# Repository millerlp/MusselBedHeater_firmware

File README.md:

# MusselBedHeater_firmware
Luke Miller, 2020

A permanent archive of this repository is stored in a Zenodo archive: https://doi.org/10.5281/zenodo.7246441 

 Firmware and hardware for Mussel Bed Heater project that Claire Windecker carried out 
 for her Masters thesis at Cal Poly Humboldt. The project consists of a circuit board 
 design that uses Arduino software to control an ATmega328P microcontroller to carry out 
 temperature monitoring and control heated artificial mussel beds. 

## Hardware design files 

Hardware_files/ contains parts lists, bill of materials, and Autocad Eagle design files. MusselBedHeater_RevG is the
most recent version, and contains all of the modifications made to the Revision F boards that were used 
in the field experiment. The heater sub-assembly board is in Heater_subassembly_revA.

## Arduino software files 

library_copies/ contains copies of the necessary Arduino libraries used to run the MusselBedHeater_firmware

Arduino programs used to run the hardware in the field are contained in:
* MusselBedHeater_6Crise/
* MusselBedHeater_field/

Utility Arduino programs used to set up the boards initially are in:
* serial_number_generator/
* settime_Serial/

### Reference mussels

Part of the design included the need to have a reference temperature, which the heated mussels would then 
be heated above by 2C or 6C. Reference mussels used a MAX31820 OneWire temperature sensor, which was 
embedded in artificial epoxy mussels as well. One control board can monitor 4 reference temperature sensors. 
The software averages the temperatures from the available reference mussels and uses that value to establish
the 'ambient' mussel temperature. Heated mussels were then heated to a target temperature increase, 2 or 6 degrees
Celsius above ambient. 

A TO-92 package MAX31820 is shown wired into the cable that will lead back to the battery box and controller board.

## Heating assembly 

The heated artificial mussels were built using 38 Gauge Nichrome 80 wire (14 ohm per meter) in a 
length of 300 mm (~12 inches) wrapped around the Heater_subassembly_revA circuit board. This arrangement
should consume a maximum of about 3 Watts at 13V supply, but the circuit board is designed to pulse width
modulate the supply voltage to the heater and provide a basic PID control algorithm to achieve a desired 
target temperature above ambient. 

The cable supplying power to the heater coil also connected to a 6800 ohm 3% NTC thermistor, which was
used to measure the temperature of the artificial mussel. The thermistor was wired in a half-bridge
configured with 4700 ohm precision resistors found on the main MusselBedHeater_RevG circuit board.

The thermistor and heater coil board were eventually cast into the middle of an epoxy artificial mussel. 

One control board can control up to 16 heated mussels, including measuring their thermistor temperatures.

## Acknowledgements 
Funding from the National Science Foundation grants OCE-1904184 and OCE-1904185 helped support Luke Miller 
during the development of this hardware and software.

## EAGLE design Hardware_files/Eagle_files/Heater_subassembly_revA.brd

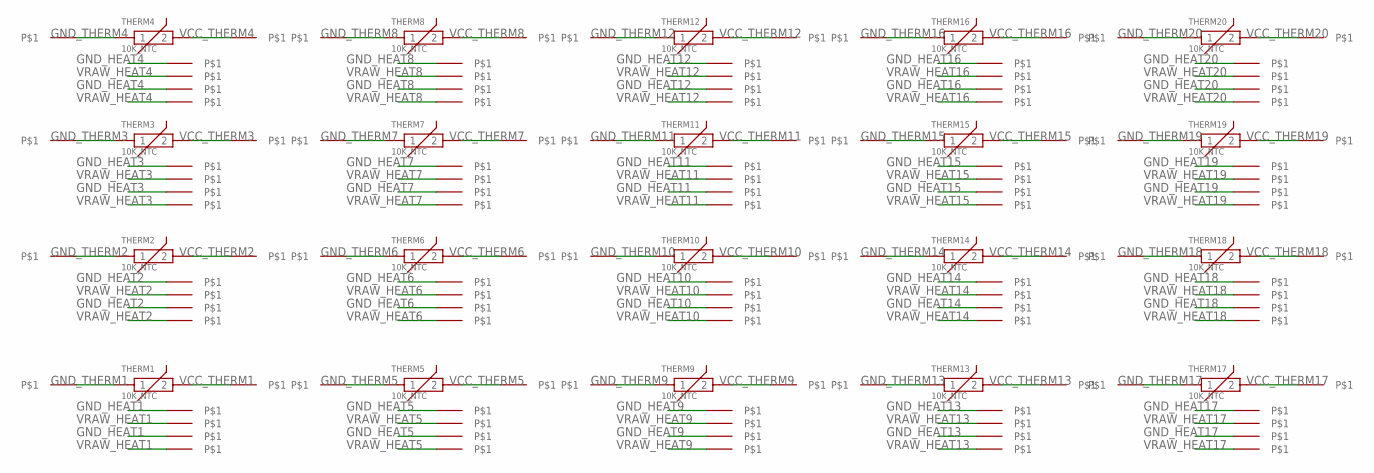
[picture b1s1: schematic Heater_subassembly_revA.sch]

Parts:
GND_HEAT1, GND_HEAT2, GND_HEAT3, GND_HEAT4, GND_HEAT5, GND_HEAT6, GND_HEAT7, GND_HEAT8, GND_HEAT9, GND_HEAT10, GND_HEAT11, GND_HEAT12, GND_HEAT13, GND_HEAT14, GND_HEAT15, GND_HEAT16, GND_HEAT17, GND_HEAT18, GND_HEAT19, GND_HEAT20: PINHD-1X1SMALL; 1X01_SMALL
GND_NICHROME1, GND_NICHROME2, GND_NICHROME3, GND_NICHROME4, GND_NICHROME5, GND_NICHROME6, GND_NICHROME7, GND_NICHROME8, GND_NICHROME9, GND_NICHROME10, GND_NICHROME11, GND_NICHROME12, GND_NICHROME13, GND_NICHROME14, GND_NICHROME15, GND_NICHROME16, GND_NICHROME17, GND_NICHROME18, GND_NICHROME19, GND_NICHROME20: PINHD-1X10.7MM_DRILL; 1X01_SMALL_0.7
GND_THERM1, GND_THERM2, GND_THERM3, GND_THERM4, GND_THERM5, GND_THERM6, GND_THERM7, GND_THERM8, GND_THERM9, GND_THERM10, GND_THERM11, GND_THERM12, GND_THERM13, GND_THERM14, GND_THERM16, GND_THERM17, GND_THERM18, GND_THERM19, GND_THERM20: PINHD-1X1SMALL; 1X01_SMALL
THERM1, THERM2, THERM3, THERM4, THERM5, THERM6, THERM7, THERM8, THERM9, THERM10, THERM11, THERM12, THERM13, THERM14, THERM15, THERM16, THERM17, THERM18, THERM19, THERM20: 10K_NTC; R0603_THERMISTOR
U$30: PINHD-1X1SMALL; 1X01_SMALL
VCC_THERM1, VCC_THERM2, VCC_THERM3, VCC_THERM4, VCC_THERM5, VCC_THERM6, VCC_THERM7, VCC_THERM8, VCC_THERM9, VCC_THERM10, VCC_THERM11, VCC_THERM12, VCC_THERM13, VCC_THERM14, VCC_THERM15, VCC_THERM16, VCC_THERM17, VCC_THERM18, VCC_THERM19, VCC_THERM20: PINHD-1X1SMALL; 1X01_SMALL
VRAW_HEAT1, VRAW_HEAT2, VRAW_HEAT3, VRAW_HEAT4, VRAW_HEAT5, VRAW_HEAT6, VRAW_HEAT7, VRAW_HEAT8, VRAW_HEAT9, VRAW_HEAT10, VRAW_HEAT11, VRAW_HEAT12, VRAW_HEAT13, VRAW_HEAT14, VRAW_HEAT15, VRAW_HEAT16, VRAW_HEAT17, VRAW_HEAT18, VRAW_HEAT19, VRAW_HEAT20: PINHD-1X1SMALL; 1X01_SMALL
VRAW_NICHROME1, VRAW_NICHROME2, VRAW_NICHROME3, VRAW_NICHROME4, VRAW_NICHROME5, VRAW_NICHROME6, VRAW_NICHROME7, VRAW_NICHROME8, VRAW_NICHROME9, VRAW_NICHROME10, VRAW_NICHROME11, VRAW_NICHROME12, VRAW_NICHROME13, VRAW_NICHROME14, VRAW_NICHROME15, VRAW_NICHROME16, VRAW_NICHROME17, VRAW_NICHROME18, VRAW_NICHROME19, VRAW_NICHROME20: PINHD-1X10.7MM_DRILL; 1X01_SMALL_0.7

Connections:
GND_HEAT1: GND_HEAT1.1, GND_NICHROME1.P$1
GND_HEAT2: GND_HEAT2.1, GND_NICHROME2.P$1
GND_HEAT3: GND_HEAT3.1, GND_NICHROME3.P$1
GND_HEAT4: GND_HEAT4.1, GND_NICHROME4.P$1
GND_HEAT5: GND_HEAT5.1, GND_NICHROME5.P$1
GND_HEAT6: GND_HEAT6.1, GND_NICHROME6.P$1
GND_HEAT7: GND_HEAT7.1, GND_NICHROME7.P$1
GND_HEAT8: GND_HEAT8.1, GND_NICHROME8.P$1
GND_HEAT9: GND_HEAT9.1, GND_NICHROME9.P$1
GND_HEAT10: GND_HEAT10.1, GND_NICHROME10.P$1
GND_HEAT11: GND_HEAT11.1, GND_NICHROME11.P$1
GND_HEAT12: GND_HEAT12.1, GND_NICHROME12.P$1
GND_HEAT13: GND_HEAT13.1, GND_NICHROME13.P$1
GND_HEAT14: GND_HEAT14.1, GND_NICHROME14.P$1
GND_HEAT15: GND_HEAT15.1, GND_NICHROME15.P$1
GND_HEAT16: GND_HEAT16.1, GND_NICHROME16.P$1
GND_HEAT17: GND_HEAT17.1, GND_NICHROME17.P$1
GND_HEAT18: GND_HEAT18.1, GND_NICHROME18.P$1
GND_HEAT19: GND_HEAT19.1, GND_NICHROME19.P$1
GND_HEAT20: GND_HEAT20.1, GND_NICHROME20.P$1
GND_THERM1: GND_THERM1.1, THERM1.1
GND_THERM2: GND_THERM2.1, THERM2.1
GND_THERM3: GND_THERM3.1, THERM3.1
GND_THERM4: GND_THERM4.1, THERM4.1
GND_THERM5: GND_THERM5.1, THERM5.1
GND_THERM6: GND_THERM6.1, THERM6.1
GND_THERM7: GND_THERM7.1, THERM7.1
GND_THERM8: GND_THERM8.1, THERM8.1
GND_THERM9: GND_THERM9.1, THERM9.1
GND_THERM10: GND_THERM10.1, THERM10.1
GND_THERM11: GND_THERM11.1, THERM11.1
GND_THERM12: GND_THERM12.1, THERM12.1
GND_THERM13: GND_THERM13.1, THERM13.1
GND_THERM14: GND_THERM14.1, THERM14.1
GND_THERM15: THERM15.1, U$30.1
GND_THERM16: GND_THERM16.1, THERM16.1
GND_THERM17: GND_THERM17.1, THERM17.1
GND_THERM18: GND_THERM18.1, THERM18.1
GND_THERM19: GND_THERM19.1, THERM19.1
GND_THERM20: GND_THERM20.1, THERM20.1
VCC_THERM1: THERM1.2, VCC_THERM1.1
VCC_THERM2: THERM2.2, VCC_THERM2.1
VCC_THERM3: THERM3.2, VCC_THERM3.1
VCC_THERM4: THERM4.2, VCC_THERM4.1
VCC_THERM5: THERM5.2, VCC_THERM5.1
VCC_THERM6: THERM6.2, VCC_THERM6.1
VCC_THERM7: THERM7.2, VCC_THERM7.1
VCC_THERM8: THERM8.2, VCC_THERM8.1
VCC_THERM9: THERM9.2, VCC_THERM9.1
VCC_THERM10: THERM10.2, VCC_THERM10.1
VCC_THERM11: THERM11.2, VCC_THERM11.1
VCC_THERM12: THERM12.2, VCC_THERM12.1
VCC_THERM13: THERM13.2, VCC_THERM13.1
VCC_THERM14: THERM14.2, VCC_THERM14.1
VCC_THERM15: THERM15.2, VCC_THERM15.1
VCC_THERM16: THERM16.2, VCC_THERM16.1
VCC_THERM17: THERM17.2, VCC_THERM17.1
VCC_THERM18: THERM18.2, VCC_THERM18.1
VCC_THERM19: THERM19.2, VCC_THERM19.1
VCC_THERM20: THERM20.2, VCC_THERM20.1
VRAW_HEAT1: VRAW_HEAT1.1, VRAW_NICHROME1.P$1
VRAW_HEAT2: VRAW_HEAT2.1, VRAW_NICHROME2.P$1
VRAW_HEAT3: VRAW_HEAT3.1, VRAW_NICHROME3.P$1
VRAW_HEAT4: VRAW_HEAT4.1, VRAW_NICHROME4.P$1
VRAW_HEAT5: VRAW_HEAT5.1, VRAW_NICHROME5.P$1
VRAW_HEAT6: VRAW_HEAT6.1, VRAW_NICHROME6.P$1
VRAW_HEAT7: VRAW_HEAT7.1, VRAW_NICHROME7.P$1
VRAW_HEAT8: VRAW_HEAT8.1, VRAW_NICHROME8.P$1
VRAW_HEAT9: VRAW_HEAT9.1, VRAW_NICHROME9.P$1
VRAW_HEAT10: VRAW_HEAT10.1, VRAW_NICHROME10.P$1
VRAW_HEAT11: VRAW_HEAT11.1, VRAW_NICHROME11.P$1
VRAW_HEAT12: VRAW_HEAT12.1, VRAW_NICHROME12.P$1
VRAW_HEAT13: VRAW_HEAT13.1, VRAW_NICHROME13.P$1
VRAW_HEAT14: VRAW_HEAT14.1, VRAW_NICHROME14.P$1
VRAW_HEAT15: VRAW_HEAT15.1, VRAW_NICHROME15.P$1
VRAW_HEAT16: VRAW_HEAT16.1, VRAW_NICHROME16.P$1
VRAW_HEAT17: VRAW_HEAT17.1, VRAW_NICHROME17.P$1
VRAW_HEAT18: VRAW_HEAT18.1, VRAW_NICHROME18.P$1
VRAW_HEAT19: VRAW_HEAT19.1, VRAW_NICHROME19.P$1
VRAW_HEAT20: VRAW_HEAT20.1, VRAW_NICHROME20.P$1

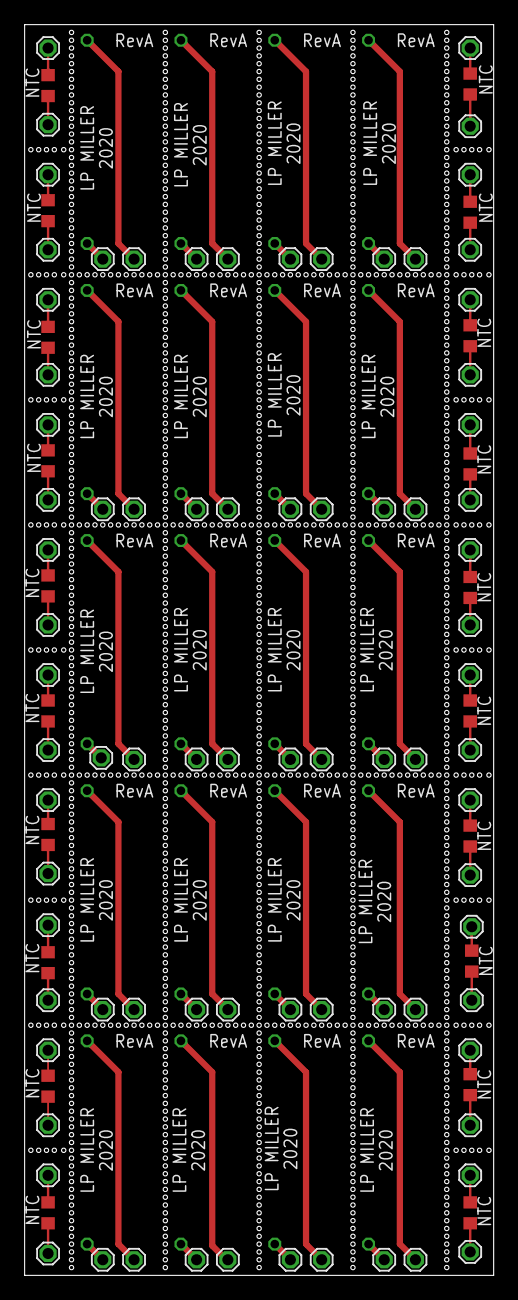
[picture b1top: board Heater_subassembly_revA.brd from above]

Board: 2 copper layers, 38.1 x 101.6 mm, 140 parts (0 on the bottom side), 80 nets.

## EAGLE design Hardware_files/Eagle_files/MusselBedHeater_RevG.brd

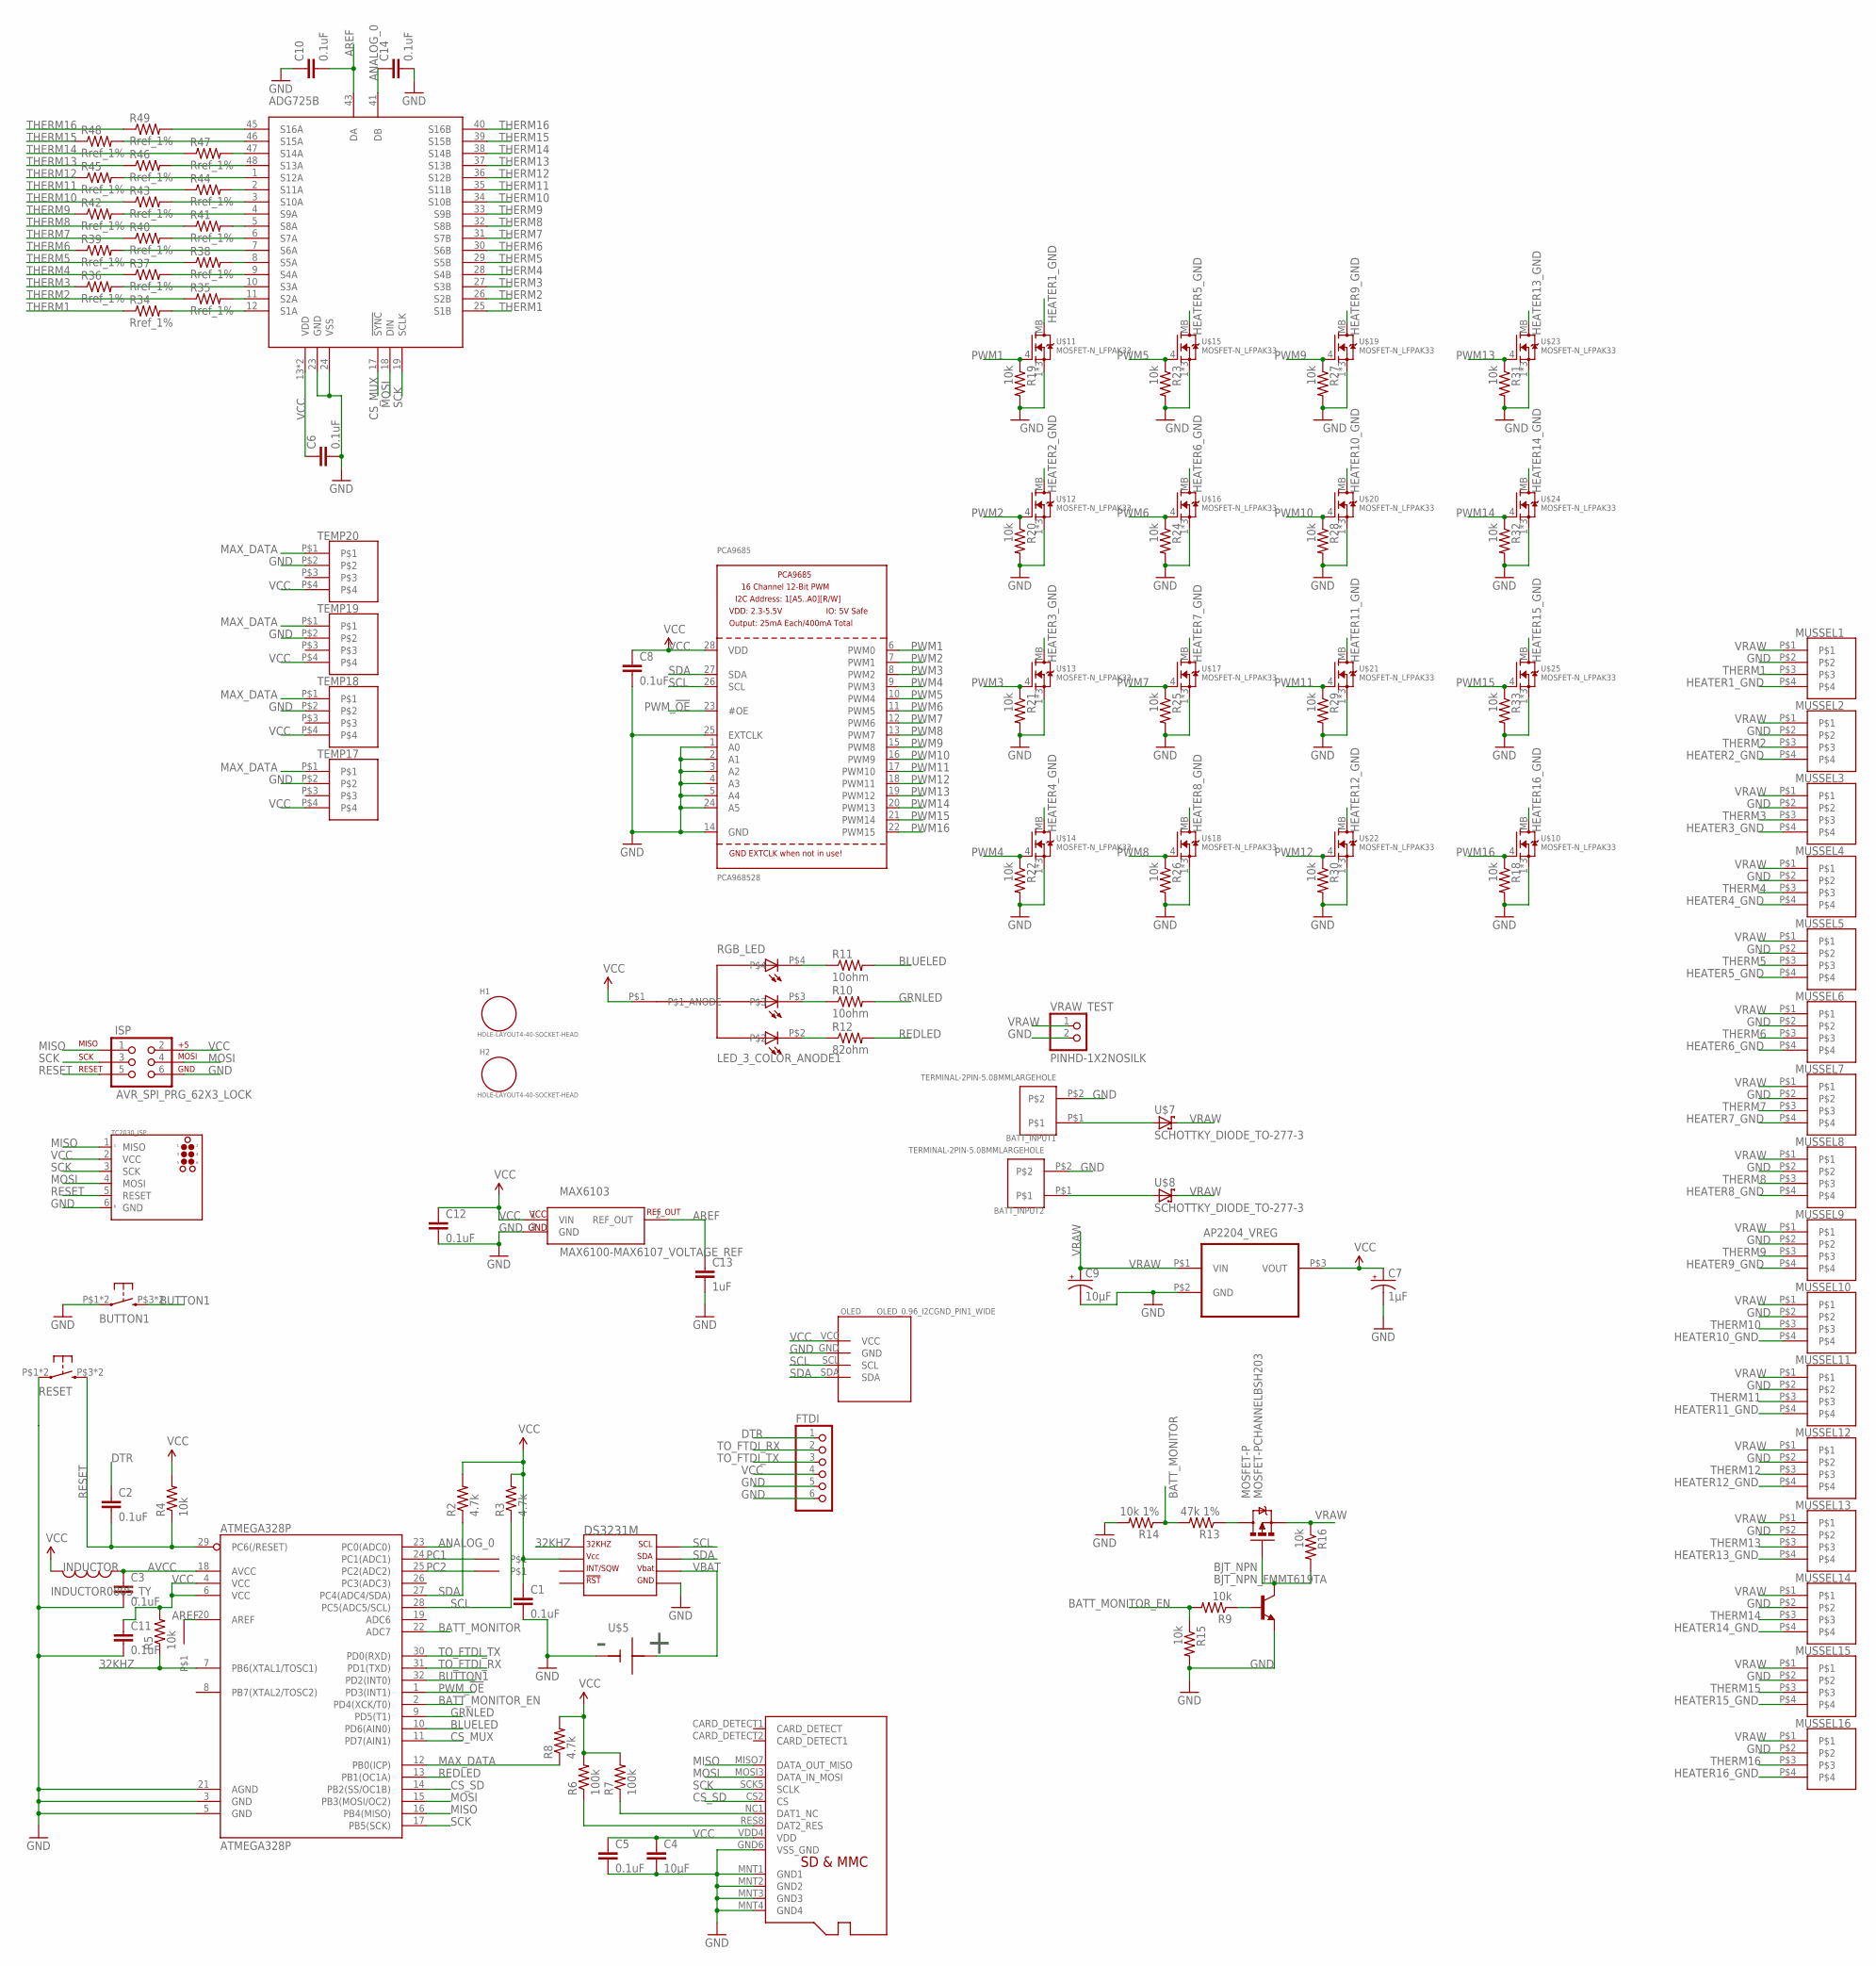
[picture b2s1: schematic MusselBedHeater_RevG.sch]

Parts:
ADG725B: ADG725_MUX; TQFP48
AP2204_VREG: AP2204R; SOT-89
AREF: PINHD-1X1STANDARD; 1X01
ATMEGA328P: ATMEGA328P; TQFP32-08
BATT_INPUT1, BATT_INPUT2: TERMINAL-2PIN-5.08MMLARGEHOLE; TERMINAL-2PIN-5.08MM_LARGEHOLE
BJT_NPN: BJT_NPN_FMMT619TA; SOT23
BUTTON1: PUSHBUTTON_DPST_SMD2SMALL; PUSHBUTTON_SPST_PTS525_SERIES
C1, C2, C3, C5, C6, C8, C10, C11, C12, C14: 0.1uF; 0603
C4: 10µF; 0603
C7: 1µF; PANASONIC_B
C9: 10µF; PANASONIC_C
C13: 1uF; 0603
DS3231M: DS3231MSOIC-8; DS3231M_SOIC8
FTDI: PINHD-1X6RA; 1X06-RIGHT_ANGLE
H1, H2: HOLE-LAYOUT4-40-SOCKET-HEAD; 4-40-SCREW-HOLE
INDUCTOR: INDUCTOR0805_TY; I_0805
ISP: AVR_SPI_PRG_62X3_LOCK; 2X3_LOCK
MAX6103: MAX6100-MAX6107_VOLTAGE_REF; SOT23-3
MOSFET-P: MOSFET-PCHANNELBSH203; SOT23-3
MUSSEL1, MUSSEL2, MUSSEL3, MUSSEL4, MUSSEL5, MUSSEL6, MUSSEL7, MUSSEL8, MUSSEL9, MUSSEL10, MUSSEL11, MUSSEL12, MUSSEL13, MUSSEL14, MUSSEL15, MUSSEL16: MOLEX_KK_254_4_PIN_HEADER; MOLEX_KK_254_4PIN_HEADER
OLED: OLED_0.96_I2CGND_PIN1_WIDE; OLED_0.96_I2C_GND_PIN1_WIDE
PC1, PC2: PINHD-1X1STANDARD; 1X01
PCA9685: PCA968528; 28-TSSOP
R2, R3, R8: 4.7k; R0603
R4, R5, R9, R15, R16, R18, R19, R20, R21, R22, R23, R24, R25, R26, R27, R28, R29, R30, R31, R32, R33: 10k; R0603
R6, R7: 100k; R0603
R10, R11: 10ohm; R0603
R12: 82ohm; R0603
R13: 47k 1%; R0603
R14: 10k 1%; R0603
R34, R35, R36, R37, R38, R39, R40, R41, R42, R43, R44, R45, R46, R47, R48, R49: Rref_1%; R0603
RESET: PUSHBUTTON_DPST_SMD2SMALL; PUSHBUTTON_SPST_PTS525_SERIES
RGB_LED: LED_3_COLOR_ANODE1; LED_RGB_SMD_1.6X1.6
TC2030_ISP: TC2030-MCP-NL
TEMP17, TEMP18, TEMP19, TEMP20: MOLEX_KK_254_4_PIN_HEADER; MOLEX_KK_254_4PIN_HEADER
U$2: MICROSD_MOLEX_REVERSECURRENT; MICROSD_SOCKET_MOLEX_REVERSEMOUNT
U$5: BATTERY_BUTTON_CELLCR1220_SMD; CR1220_BATTERY_HOLDER_SMD
U$7, U$8: SCHOTTKY_DIODE_TO-277-3; TO-277-3
U$10, U$11, U$12, U$13, U$14, U$15, U$16, U$17, U$18, U$19, U$20, U$21, U$22, U$23, U$24, U$25: MOSFET-N_LFPAK33; SOT1210
VRAW_TEST: PINHD-1X2NOSILK; 1X02_NOSILK

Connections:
32KHZ: ATMEGA328P.7 (PB6(XTAL1/TOSC1)), DS3231M.1 (P$1_32KHZ), R5.1
ANALOG_0: ADG725B.41 (DB), ATMEGA328P.23 (PC0(ADC0)), C14.1
AREF: ADG725B.43 (DA), AREF.1, ATMEGA328P.20 (AREF), C10.2, C13.1, MAX6103.2 (REF_OUT)
AVCC: ATMEGA328P.18 (AVCC), C3.1, INDUCTOR.P$1 (1)
BATT_MONITOR: ATMEGA328P.22 (ADC7), R13.2, R14.1
BATT_MONITOR_EN: ATMEGA328P.2 (PD4(XCK/T0)), R9.2, R15.1
BLUELED: ATMEGA328P.10 (PD6(AIN0)), R11.2
BUTTON1: ATMEGA328P.32 (PD2(INT0)), BUTTON1.P$3 (S), BUTTON1.P$4 (S)
CS_MUX: ADG725B.17 (!SYNC), ATMEGA328P.11 (PD7(AIN1))
CS_SD: ATMEGA328P.14 (PB2(SS/OC1B)), U$2.CS2 (CS)
DTR: C2.1, FTDI.1
GND: ADG725B.23 (GND), ADG725B.24 (VSS), AP2204_VREG.P$2 (GND), ATMEGA328P.3 (GND), ATMEGA328P.5 (GND), ATMEGA328P.21 (AGND), BATT_INPUT1.P$2, BATT_INPUT2.P$2, BJT_NPN.2 (E), BUTTON1.P$1, BUTTON1.P$2, C1.2, C3.2, C4.2, C5.2, C6.2, C7.-, C8.2, C9.-, C10.1, C11.2, C12.2, C13.2, C14.2, DS3231M.5 (P$5_GND), FTDI.5, FTDI.6, ISP.6, MAX6103.3 (GND), MUSSEL1.P$2, MUSSEL2.P$2, MUSSEL3.P$2, MUSSEL4.P$2, MUSSEL5.P$2, MUSSEL6.P$2, MUSSEL7.P$2, MUSSEL8.P$2, MUSSEL9.P$2, MUSSEL10.P$2, MUSSEL11.P$2, MUSSEL12.P$2, MUSSEL13.P$2, MUSSEL14.P$2, MUSSEL15.P$2, MUSSEL16.P$2, OLED.GND, PCA9685.1 (A0), PCA9685.2 (A1), PCA9685.3 (A2), PCA9685.4 (A3), PCA9685.5 (A4), PCA9685.14 (GND), PCA9685.24 (A5), PCA9685.25 (EXTCLK), R14.2, R15.2, R18.2, R19.2, R20.2, R21.2, R22.2, R23.2, R24.2, R25.2, R26.2, R27.2, R28.2, R29.2, R30.2, R31.2, R32.2, R33.2, RESET.P$1, RESET.P$2, TC2030_ISP.6 (GND), TEMP17.P$2, TEMP18.P$2, TEMP19.P$2, TEMP20.P$2, U$2.GND6 (VSS_GND), U$2.MNT1 (GND1), U$2.MNT2 (GND2), U$2.MNT3 (GND3), U$2.MNT4 (GND4), U$5.GND, U$10.1 (S), U$10.2 (S), U$10.3 (S), U$11.1 (S), U$11.2 (S), U$11.3 (S), U$12.1 (S), U$12.2 (S), U$12.3 (S), U$13.1 (S), U$13.2 (S), U$13.3 (S), U$14.1 (S), U$14.2 (S), U$14.3 (S), U$15.1 (S), U$15.2 (S), U$15.3 (S), U$16.1 (S), U$16.2 (S), U$16.3 (S), U$17.1 (S), U$17.2 (S), U$17.3 (S), U$18.1 (S), U$18.2 (S), U$18.3 (S), U$19.1 (S), U$19.2 (S), U$19.3 (S), U$20.1 (S), U$20.2 (S), U$20.3 (S), U$21.1 (S), U$21.2 (S), U$21.3 (S), U$22.1 (S), U$22.2 (S), U$22.3 (S), U$23.1 (S), U$23.2 (S), U$23.3 (S), U$24.1 (S), U$24.2 (S), U$24.3 (S), U$25.1 (S), U$25.2 (S), U$25.3 (S), VRAW_TEST.2
GRNLED: ATMEGA328P.9 (PD5(T1)), R10.2
HEATER1_GND: MUSSEL1.P$4, U$11.MB (D)
HEATER2_GND: MUSSEL2.P$4, U$12.MB (D)
HEATER3_GND: MUSSEL3.P$4, U$13.MB (D)
HEATER4_GND: MUSSEL4.P$4, U$14.MB (D)
HEATER5_GND: MUSSEL5.P$4, U$15.MB (D)
HEATER6_GND: MUSSEL6.P$4, U$16.MB (D)
HEATER7_GND: MUSSEL7.P$4, U$17.MB (D)
HEATER8_GND: MUSSEL8.P$4, U$18.MB (D)
HEATER9_GND: MUSSEL9.P$4, U$19.MB (D)
HEATER10_GND: MUSSEL10.P$4, U$20.MB (D)
HEATER11_GND: MUSSEL11.P$4, U$21.MB (D)
HEATER12_GND: MUSSEL12.P$4, U$22.MB (D)
HEATER13_GND: MUSSEL13.P$4, U$23.MB (D)
HEATER14_GND: MUSSEL14.P$4, U$24.MB (D)
HEATER15_GND: MUSSEL15.P$4, U$25.MB (D)
HEATER16_GND: MUSSEL16.P$4, U$10.MB (D)
MAX_DATA: ATMEGA328P.12 (PB0(ICP)), R8.1, TEMP17.P$1, TEMP18.P$1, TEMP19.P$1, TEMP20.P$1
MISO: ATMEGA328P.16 (PB4(MISO)), ISP.1, TC2030_ISP.1 (MISO), U$2.MISO7 (DATA_OUT_MISO)
MOSI: ADG725B.18 (DIN), ATMEGA328P.15 (PB3(MOSI/OC2)), ISP.4, TC2030_ISP.4 (MOSI), U$2.MOSI3 (DATA_IN_MOSI)
unnamed: BATT_INPUT1.P$1, U$7.P$1 (A), U$7.P$2 (A)
unnamed: BATT_INPUT2.P$1, U$8.P$1 (A), U$8.P$2 (A)
unnamed: R7.1, U$2.NC1 (DAT1_NC)
unnamed: R6.1, U$2.RES8 (DAT2_RES)
unnamed: BJT_NPN.3 (C), MOSFET-P.1 (G), R16.2
unnamed: BJT_NPN.1 (B), R9.1
unnamed: ADG725B.12 (S1A), R34.2
unnamed: R12.1, RGB_LED.P$2
unnamed: R10.1, RGB_LED.P$3
unnamed: R11.1, RGB_LED.P$4
unnamed: MOSFET-P.3 (D), R13.1
unnamed: ADG725B.11 (S2A), R35.2
unnamed: ADG725B.10 (S3A), R36.2
unnamed: ADG725B.9 (S4A), R37.2
unnamed: ADG725B.8 (S5A), R38.2
unnamed: ADG725B.7 (S6A), R39.2
unnamed: ADG725B.6 (S7A), R40.2
unnamed: ADG725B.5 (S8A), R41.2
unnamed: ADG725B.4 (S9A), R42.2
unnamed: ADG725B.3 (S10A), R43.2
unnamed: ADG725B.2 (S11A), R44.2
unnamed: ADG725B.1 (S12A), R45.2
unnamed: ADG725B.48 (S13A), R46.2
unnamed: ADG725B.47 (S14A), R47.2
unnamed: ADG725B.46 (S15A), R48.2
unnamed: ADG725B.45 (S16A), R49.2
PC1: ATMEGA328P.24 (PC1(ADC1)), PC1.1
PC2: ATMEGA328P.25 (PC2(ADC2)), PC2.1
PWM1: PCA9685.6 (PWM0), R19.1, U$11.4 (G)
PWM2: PCA9685.7 (PWM1), R20.1, U$12.4 (G)
PWM3: PCA9685.8 (PWM2), R21.1, U$13.4 (G)
PWM4: PCA9685.9 (PWM3), R22.1, U$14.4 (G)
PWM5: PCA9685.10 (PWM4), R23.1, U$15.4 (G)
PWM6: PCA9685.11 (PWM5), R24.1, U$16.4 (G)
PWM7: PCA9685.12 (PWM6), R25.1, U$17.4 (G)
PWM8: PCA9685.13 (PWM7), R26.1, U$18.4 (G)
PWM9: PCA9685.15 (PWM8), R27.1, U$19.4 (G)
PWM10: PCA9685.16 (PWM9), R28.1, U$20.4 (G)
PWM11: PCA9685.17 (PWM10), R29.1, U$21.4 (G)
PWM12: PCA9685.18 (PWM11), R30.1, U$22.4 (G)
PWM13: PCA9685.19 (PWM12), R31.1, U$23.4 (G)
PWM14: PCA9685.20 (PWM13), R32.1, U$24.4 (G)
PWM15: PCA9685.21 (PWM14), R33.1, U$25.4 (G)
PWM16: PCA9685.22 (PWM15), R18.1, U$10.4 (G)
PWM_!OE: ATMEGA328P.1 (PD3(INT1)), PCA9685.23 (#OE)
REDLED: ATMEGA328P.13 (PB1(OC1A)), R12.2
RESET: ATMEGA328P.29 (PC6(/RESET)), C2.2, ISP.5, R4.1, RESET.P$3 (S), RESET.P$4 (S), TC2030_ISP.5 (RESET)
SCK: ADG725B.19 (SCLK), ATMEGA328P.17 (PB5(SCK)), ISP.3, TC2030_ISP.3 (SCK), U$2.SCK5 (SCLK)
SCL: ATMEGA328P.28 (PC5(ADC5/SCL)), DS3231M.8 (P$8_SCL), OLED.SCL, PCA9685.26 (SCL), R3.1
SDA: ATMEGA328P.27 (PC4(ADC4/SDA)), DS3231M.7 (P$7_SDA), OLED.SDA, PCA9685.27 (SDA), R2.1
THERM1: ADG725B.25 (S1B), MUSSEL1.P$3, R34.1
THERM2: ADG725B.26 (S2B), MUSSEL2.P$3, R35.1
THERM3: ADG725B.27 (S3B), MUSSEL3.P$3, R36.1
THERM4: ADG725B.28 (S4B), MUSSEL4.P$3, R37.1
THERM5: ADG725B.29 (S5B), MUSSEL5.P$3, R38.1
THERM6: ADG725B.30 (S6B), MUSSEL6.P$3, R39.1
THERM7: ADG725B.31 (S7B), MUSSEL7.P$3, R40.1
THERM8: ADG725B.32 (S8B), MUSSEL8.P$3, R41.1
THERM9: ADG725B.33 (S9B), MUSSEL9.P$3, R42.1
THERM10: ADG725B.34 (S10B), MUSSEL10.P$3, R43.1
THERM11: ADG725B.35 (S11B), MUSSEL11.P$3, R44.1
THERM12: ADG725B.36 (S12B), MUSSEL12.P$3, R45.1
THERM13: ADG725B.37 (S13B), MUSSEL13.P$3, R46.1
THERM14: ADG725B.38 (S14B), MUSSEL14.P$3, R47.1
THERM15: ADG725B.39 (S15B), MUSSEL15.P$3, R48.1
THERM16: ADG725B.40 (S16B), MUSSEL16.P$3, R49.1
TO_FTDI_RX: ATMEGA328P.31 (PD1(TXD)), FTDI.2
TO_FTDI_TX: ATMEGA328P.30 (PD0(RXD)), FTDI.3
VBAT: DS3231M.6 (P$6_VBAT), U$5.P$1 (VBAT), U$5.P$2 (VBAT)
VCC: ADG725B.13 (VDD), ADG725B.14 (VDD), AP2204_VREG.P$3 (VOUT), ATMEGA328P.4 (VCC), ATMEGA328P.6 (VCC), C1.1, C4.1, C5.1, C6.1, C7.+, C8.1, C11.1, C12.1, DS3231M.2 (P$2_VCC), FTDI.4, INDUCTOR.P$2 (2), ISP.2, MAX6103.1 (VIN), OLED.VCC, PCA9685.28 (VDD), R2.2, R3.2, R4.2, R5.2, R6.2, R7.2, R8.2, RGB_LED.P$1 (P$1_ANODE), TC2030_ISP.2 (VCC), TEMP17.P$4, TEMP18.P$4, TEMP19.P$4, TEMP20.P$4, U$2.VDD4 (VDD)
VRAW: AP2204_VREG.P$1 (VIN), C9.+, MOSFET-P.2 (S), MUSSEL1.P$1, MUSSEL2.P$1, MUSSEL3.P$1, MUSSEL4.P$1, MUSSEL5.P$1, MUSSEL6.P$1, MUSSEL7.P$1, MUSSEL8.P$1, MUSSEL9.P$1, MUSSEL10.P$1, MUSSEL11.P$1, MUSSEL12.P$1, MUSSEL13.P$1, MUSSEL14.P$1, MUSSEL15.P$1, MUSSEL16.P$1, R16.1, U$7.P$3 (C), U$8.P$3 (C), VRAW_TEST.1

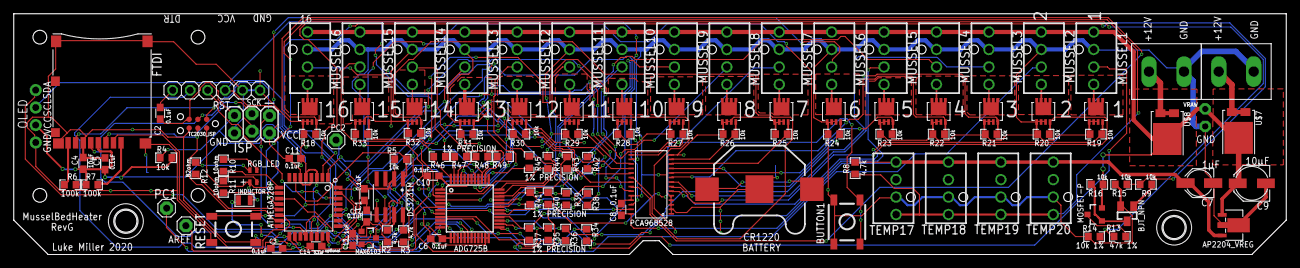
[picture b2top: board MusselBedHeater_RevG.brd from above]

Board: 2 copper layers, 185.0 x 35.0 mm, 125 parts (0 on the bottom side), 103 nets.

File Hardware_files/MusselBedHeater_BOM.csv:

"Revision F, G MusselBedHeater",,,,
Qty,Value,Device,Package,Parts
1,,PINHD-1X6RA,1X06-RIGHT_ANGLE,FTDI
10,0.1uF,CAP0603,0603,"C1, C2, C3, C5, C6, C8, C10, C11, C12, C14"
2,100k 5%,RESISTOR_SMDR0603,R0603,"R6, R7"
21,10k  5%,RESISTOR_SMDR0603,R0603,"R4, R5, R9, R15, R16, R18, R19, R20, R21, R22, R23, R24, R25, R26, R27, R28, R29, R30, R31, R32, R33"
1,10k 1% or 0.5%,RESISTOR_SMDR0603 (battery reference),R0603,R14
2,10 ohm,RESISTOR_SMDR0603 (LED),R0603,"R10, R11"
1,10 µF,CAP0603,0603,C4
1,10 µF,CPOL-USC,PANASONIC_C,C9
1,1uF,CAP0603,0603,C13
1,1µF,CPOL-USB,PANASONIC_B,C7
3,4.7k 5%,RESISTOR_SMDR0603 (pull-ups),R0603,"R2, R3, R8"
16,4.7 kohm 1%,RESISTOR_SMDR0603 (thermistor ref),R0603,"R34, R35, R36, R37, R38, R39, R40, R41, R42, R43, R44, R45, R46, R47, R48, R49"
1,47k 1% or 0.5%,RESISTOR_SMDR0603 (battery reference),R0603,R13
1,82 ohm,RESISTOR_SMDR0603 (LED),R0603,R12
1,ADG725_MUX,ADG725_MUX,TQFP48,ADG725B
1,AP2204R,AP2204R  Voltage regulator,SOT-89,AP2204_VREG
1,ATMEGA328P,ATMEGA328_SMT,TQFP32-08,ATMEGA328P
1,AVR_SPI_PRG_62X3_LOCK,"2x3 header 0.1"" pitch",2X3_LOCK,ISP
1,BATTERY_BUTTON_CELLCR1220_SMD,BATTERY_BUTTON_CELLCR1220_SMD,CR1220_BATTERY_HOLDER_SMD,U$5
1,BJT_NPN_FMMT619TA,BJT_NPN_FMMT619TA (battery monitor),SOT23,BJT_NPN
1,MOSFET-PCHANNELBSH203,MOSFET-PCHANNELBSH203 (battery monitor),SOT23-3,MOSFET-P
1,DS3231MSOIC-8,DS3231MSOIC-8 (real time clock),DS3231M_SOIC8,DS3231M
1,INDUCTOR0805_TY,INDUCTOR0805_TY,I_0805,INDUCTOR
1,LED_3_COLOR_ANODE1,LED_3_COLOR_ANODE1,LED_RGB_SMD_1.6X1.6,RGB_LED
1,MAX6100-MAX6107_VOLTAGE_REF,MAX6100-MAX6107_VOLTAGE_REF,SOT23-3,MAX6103
1,MICROSD_MOLEX_REVERSECURRENT,MICROSD_MOLEX_REVERSECURRENT,MICROSD_SOCKET_MOLEX_REVERSEMOUNT,U$2
16,MOSFET-N_LFPAK33,MOSFET-N_LFPAK33,SOT1210,"U$10, U$11, U$12, U$13, U$14, U$15, U$16, U$17, U$18, U$19, U$20, U$21, U$22, U$23, U$24, U$25"
1,OLED_0.96_I2CGND_PIN1_WIDE,"4-pin 0.1"" pitch header",OLED_0.96_I2C_GND_PIN1_WIDE,OLED
1,PCA968528,PCA968528,28-TSSOP,PCA9685
2,PUSHBUTTON_DPST_SMD2SMALL,PUSHBUTTON_DPST_SMD2SMALL,PUSHBUTTON_SPST_PTS525_SERIES,"BUTTON1, RESET"
2,SCHOTTKY_DIODE_TO-277-3,SCHOTTKY_DIODE_TO-277-3,TO-277-3,"U$7, U$8"
2,TERMINAL-2PIN-5.08MMLARGEHOLE,TERMINAL-2PIN-5.08MMLARGEHOLE,TERMINAL-2PIN-5.08MM_LARGEHOLE,"BATT_INPUT1, BATT_INPUT2"

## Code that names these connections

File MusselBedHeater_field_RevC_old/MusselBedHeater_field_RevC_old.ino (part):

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                              // this value should be negative, to make the reported temperature
                              // closer to the lower (true) calibration temperature. Units: Celsius
//-----------------------------------------------------------------------------------
#define BUTTON1 2     // BUTTON1 on INT0, pin PD2

//---------------------------------------------------------------------------
// Thermistor multiplexer setup
// Multiplexer macros for use in reading thermistors in heated mussels
#define CS_MUX 7 // Arduino pin D7 connected to ADG725 SYNC pin
#define THERM A0 // Arduino analog input pin A0, reading thermistors from ADG725 mux
#define SPI_SPEED 4000000 // Desired SPI speed for talking to ADG725
// Create Thermistor object
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// PCA9685 pulse width modulation driver chip
// Called this way, uses the default address 0x40
Adafruit_PWMServoDriver pwm = Adafruit_PWMServoDriver();
#define PWM_OE 3 // PWM driver output enable pin (active low), connected to ATmega pin PD3

//-------------------------------------------------------------
// SD card
#define CS_SD 10 // Pin used for SD card
SdFat sd;
SdFile logfile; // This is the file object that will be written to
// Declare initial name for output files written to SD card
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
//------------------------------------------------------------
//  Battery monitor 
#define BATT_MONITOR A7  // analog input channel to sense battery voltage
#define BATT_MONITOR_EN 4 // digital output channel to turn on battery voltage check
float dividerRatio = 5.7; // Ratio of voltage divider (47k + 10k) / 10k = 5.7
// The refVoltage needs to be measured individually for each board (use a 
// voltmeter and measure at the AVCC and GND pins on the board). Enter the 
// voltage value here. 
float refVoltage = 3.00; // Voltage at RevC AVCC pin on ATmega microcontroller, measured per board
float batteryVolts = 0; // Estimated battery voltage returned from readBatteryVoltage function
bool lowVoltageFlag = false;
byte lowVoltageCounter = 0;
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  Serial.println(F("Hello"));
//  analogReference(EXTERNAL); // RevC boards just use Vcc as analog reference voltage
  // Set BUTTON1 as an input
  pinMode(BUTTON1, INPUT_PULLUP);
  // Battery monitor pins
  pinMode(BATT_MONITOR, INPUT);
  pinMode(BATT_MONITOR_EN, OUTPUT);
  // PWM chip pin
  pinMode(PWM_OE, OUTPUT);
  digitalWrite(PWM_OE, LOW); // Enable PWM chip
  // SPI bus pins
  pinMode(CS_SD, OUTPUT); // declare as output so that SPI library plays nice
  pinMode(CS_MUX, OUTPUT); // Set CS_MUX pin as output for ADG725 SYNC
  // Thermistor analog input pin
  pinMode(THERM, INPUT); // Analog input from ADG725
  
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
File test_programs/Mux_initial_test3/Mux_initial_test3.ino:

/*
 * Mux_initial_test3.ino
 * Luke Miller 2020
 * 
 * Testing with MusselBedHeater RevC hardware
 * Tested working for thermistor channel 1,2
 * 
 * Analog input on pin A0 (PC0)
 * ADG725 MUX SYNC pin connected to D7 (PD7)
 */

#include <SPI.h>
#include "MusselBedHeaterlib.h"

#define CS_MUX 7 // Arduino pin D7 connected to ADG725 SYNC pin
#define CS_SD 10 // Pin used for SD card
#define THERM A0 // Arduino analog input pin A0, reading thermistors from ADG725 mux
#define SPI_SPEED 4000000 // Desired SPI speed for talking to ADG725

ADG725 mux; // create ADG725 multiplexer object
uint8_t ADGchannel = 0x00; // initial value to activate ADG725 channel S1

void setup() {
  Serial.begin(57600);
  pinMode(CS_SD, OUTPUT); // declare as output so that SPI library plays nice
  pinMode(CS_MUX, OUTPUT); // Set CS_MUX pin as output for ADG725 SYNC
  pinMode(THERM, INPUT); // Analog input from ADG725
  
  SPI.begin();
  mux.begin(CS_MUX, SPI_SPEED); // Set up multiplexer
  mux.setADG725channel(ADGchannel); // Activate channel stored in ADGchannel variable
}

void loop() {
  delay(100);
  unsigned int thermRaw = analogRead(THERM);
  Serial.println(thermRaw);

}

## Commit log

2020-03-24 Adding some basic info
2020-03-24 Basic working example
    Reading 2 sensors on RevC hardware
2020-03-25 Updated MAX31820 test sketch
    Reads from up to 4 MAX31820 devices on RevC hardware
2020-03-25 Add some links to libraries
2020-03-26 Keeping an archive copy
2020-03-27 Basic working channel selection
2020-03-29 Moving SPI code to a function
2020-03-29 Testing NTC_Thermistor library
2020-03-30 Calling new library multiplexer func.
2020-03-30 Working thermistor temperature
2020-03-30 Add some urls
2020-03-30 Working reading of multiple thermistors
2020-03-31 Commenting out some timing stuff
2020-04-01 Not working,
    Trying to implement MAX31820 functions in the MusselBedHeaterlib library, but probably failing at passing arrays properly.
2020-04-01 Basic example with NTC_Thermistor lib
2020-04-03 Sort of working, lots TODO
2020-04-03 Basic 1-channel PWM test, works
2020-04-04 PWM and PID libraries archived
2020-04-04 Reading MAX and thermistors
    Need to implement multiple PIDs, and interface with PWM chip to manipulate heaters.
2020-04-10 Making some stuff into globals
    See Serial print statements at the bottom for the troubleshooting. Seems to be a minimal working example for one channel currently.
2020-04-10 Including PWM for 1 channel
2020-04-10 New test sketch
    Incorporating multiple PID objects.
2020-04-10 Cleaning up arrays and globals
    Added variable to set targeted temperature increase over reference mussel temperature.
2020-04-12 Basic PID function working
    Put a stripped-down version of the PID library into MusselBedHeaterlib to try to keep under the memory limits of the ATmega328p. This basic verison works, but needs full implementation of the SD card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
2020-04-14 Adding this so it's available to users
2020-04-14 Potentially working full prototype
    NEEDS TESTING - saves data to card, calculates tide etc. Need to tune PID routine, test battery monitoring, testing heating routine with working mussels, flash LEDs for status updates
2020-04-15 TODO: implement the temperature filtering
2020-04-15 Add TODO
2020-04-19 Not tested - basic temp display
    Could be used to test thermistor calibration against the MAX31820 temperature sensors.
2020-04-20 More TODO
2020-04-20 Added code to switch PonE or PonM
2020-04-22 Modifying thermistor read routine
    Adding some conditional if statements to make sure we can recover from a case where a thermistor goes offline temporarily and then starts working again.
2020-04-22 Testing new thermistors
2020-04-27 Creating this for heater project
2020-04-29 Setting additional pins appropriately
    Make sure the PWM chip output enable pin is set as an output, pulled low.
2020-04-29 PWM_OE! set as output, low.
    Also removing the tide height prediction routine here since it's not really necessary for tuning/testing purposes. Added MACROs to change serial monitor output style for the monitor vs. plotter. Defi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
2020-07-06 Not yet working with 4809
2020-07-06 Basic blink for 3-color RGB LED
2020-07-06 Use to check function of MAX31820 sensors
2020-07-06 new board
2020-07-06 Testing updates
2020-07-10 Ignore, new boards
2020-07-27 testing battery monitor circuit
2020-07-27 Show MAX31820 temperatures
2020-07-27 Updating for RevF hardware
2020-07-27 Not all that useful
2020-07-27 Test run with 16 sensors
2020-07-27 Updating for RevF hardware
    Clearing up some warnings as well
2020-08-10 Accumulating library copies
2020-08-10 Moving to top level folder
2021-04-07 Fixing setpoint recording, changed tide threshold
2021-04-26 New field version
    Multiple changes and a new file name:
    1. Fixed a probable bug in the STATE_IDLE transition to STATE_HEATING with a reversed < sign
    2. Adding output of predicted tide height and current program state to the SD card - NOTE: This also comes with a modification to the MusselBedHeaterlib library, so update that also
    3. Added continuous updating of pidSetpoint value when in STATE_OFF, since it wasn't doing that
2021-04-26 Adding decrement to lowVoltageCounter
    Trying to force the routine to only enter STATE_OFF if the battery voltage stays below the low voltage threshold for 5 consecutive minutes, instead of just hitting the low threshold 5 times total per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
2021-05-11 Adding explicit pwm shutdowns
2021-05-18 Working SD card test on 4809
    Must use current MegaCoreX (1.0.8) and SdFat-beta v2.1 to get this working.
2021-06-02 Making version of old RevC board
2021-06-07 Adding thermistor calibration correction
    Adding the variable therm_correction to allow for a manual correction of all of the recorded thermistor temperatures (one value applied to all 16 thermistors).
2021-06-09 Trying to cure multiple sd writes per second
2021-06-09 Moving line down to proper place in preamble
2021-06-11 Revert "Moving line down to proper place in preamble"
    This reverts commit a812ee768645219e548e7353090ddd99c12c71b0.
2021-06-11 Revert "Trying to cure multiple sd writes per second"
    This reverts commit ecdc2e03294d2bc0dd0302e914ff7a0c12873a97.
2021-07-19 Update for new board
2021-07-19 Showing output on Serial monitor
2021-07-21 Adding comments
2022-10-24 Latest hardware revision files
2022-10-24 Parts lists updated 2022
2022-10-24 Image files
2022-10-24 Removing nonfunctional branch
2022-10-24 Prettying up the readme
2022-10-24 Cropped
2022-10-24 Heater coil board design
2022-10-24 Heater coil info
2022-10-24 Section headings
2022-10-24 More description of the heater
2022-10-24 Reference details
2022-10-24 Pic of MAX31820
2022-10-24 New pic
2022-11-08 Adding Zenodo doi
2022-11-08 Funding ack.

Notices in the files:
parts and their libraries:
miller: ©2009 ROFA.cz - modified and updated by Robert Darlington ‹rdarlington@gmail.com›
